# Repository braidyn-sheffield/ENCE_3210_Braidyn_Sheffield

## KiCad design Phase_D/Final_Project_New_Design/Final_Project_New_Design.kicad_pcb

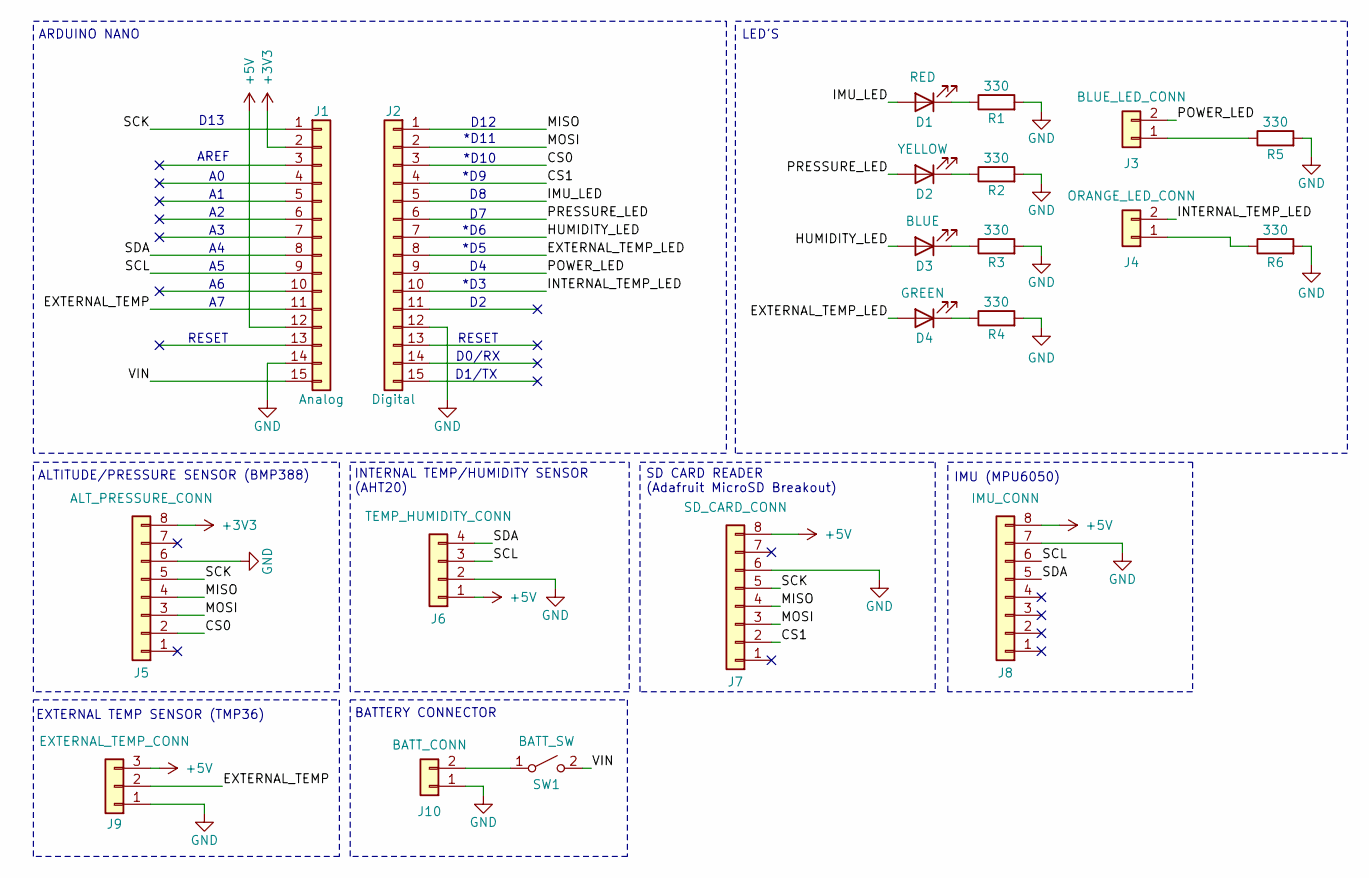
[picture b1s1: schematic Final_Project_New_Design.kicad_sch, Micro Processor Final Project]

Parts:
D1: RED; LED_D5.0mm
D2: YELLOW; LED_D5.0mm
D3: BLUE; LED_D5.0mm
D4: GREEN; LED_D5.0mm
J1: Analog; PinHeader_1x15_P2.54mm_Vertical
J2: Digital; PinHeader_1x15_P2.54mm_Vertical
J3: BLUE_LED_CONN; JST_PH_B2B-PH-K_1x02_P2.00mm_Vertical
J4: ORANGE_LED_CONN; JST_PH_B2B-PH-K_1x02_P2.00mm_Vertical
J5: ALT_PRESSURE_CONN; PinSocket_1x08_P2.54mm_Vertical
J6: TEMP_HUMIDITY_CONN; PinSocket_1x04_P2.54mm_Vertical
J7: SD_CARD_CONN; PinSocket_1x08_P2.54mm_Vertical
J8: IMU_CONN; PinSocket_1x08_P2.54mm_Vertical
J9: EXTERNAL_TEMP_CONN; JST_PH_B3B-PH-K_1x03_P2.00mm_Vertical
J10: BATT_CONN; Molex_KK-254_AE-6410-02A_1x02_P2.54mm_Vertical
R1, R2, R3, R4, R5, R6: 330; R_Axial_DIN0207_L6.3mm_D2.5mm_P7.62mm_Horizontal
SW1: BATT_SW; Toggle_SW

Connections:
+3V3: J1.2, J5.8
+5V: J1.12, J6.1, J7.8, J8.8, J9.3
/CS0: J2.3, J5.2
/CS1: J2.4, J7.2
/EXTERNAL_TEMP: J1.11, J9.2
/EXTERNAL_TEMP_LED: D4.2 (A), J2.8
/HUMIDITY_LED: D3.2 (A), J2.7
/IMU_LED: D1.2 (A), J2.5
/INTERNAL_TEMP_LED: J2.10, J4.2
/MISO: J2.1, J5.4, J7.4
/MOSI: J2.2, J5.3, J7.3
/POWER_LED: J2.9, J3.2
/PRESSURE_LED: D2.2 (A), J2.6
/SCK: J1.1, J5.5, J7.5
/SCL: J1.9, J6.3, J8.6
/SDA: J1.8, J6.4, J8.5
/VIN: J1.15, SW1.2 (B)
GND: J1.14, J2.12, J5.6, J6.2, J7.6, J8.7, J9.1, J10.1, R1.2, R2.2, R3.2, R4.2, R5.2, R6.2
unnamed: D1.1 (K), R1.1
unnamed: D2.1 (K), R2.1
unnamed: D3.1 (K), R3.1
unnamed: D4.1 (K), R4.1
unnamed: J3.1, R5.1
unnamed: J4.1, R6.1
unnamed: J10.2, SW1.1 (A)

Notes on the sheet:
D0/RX
D13
ALTITUDE/PRESSURE SENSOR (BMP388)
D1/TX
SD CARD READER (Adafruit MicroSD Breakout)
INTERNAL TEMP/HUMIDITY SENSOR (AHT20)
EXTERNAL TEMP SENSOR (TMP36)
*D9
RESET
*D10
IMU (MPU6050)
BATTERY CONNECTOR
D12
*D5
ARDUINO NANO
*D3
*D11
AREF
LED'S
*D6

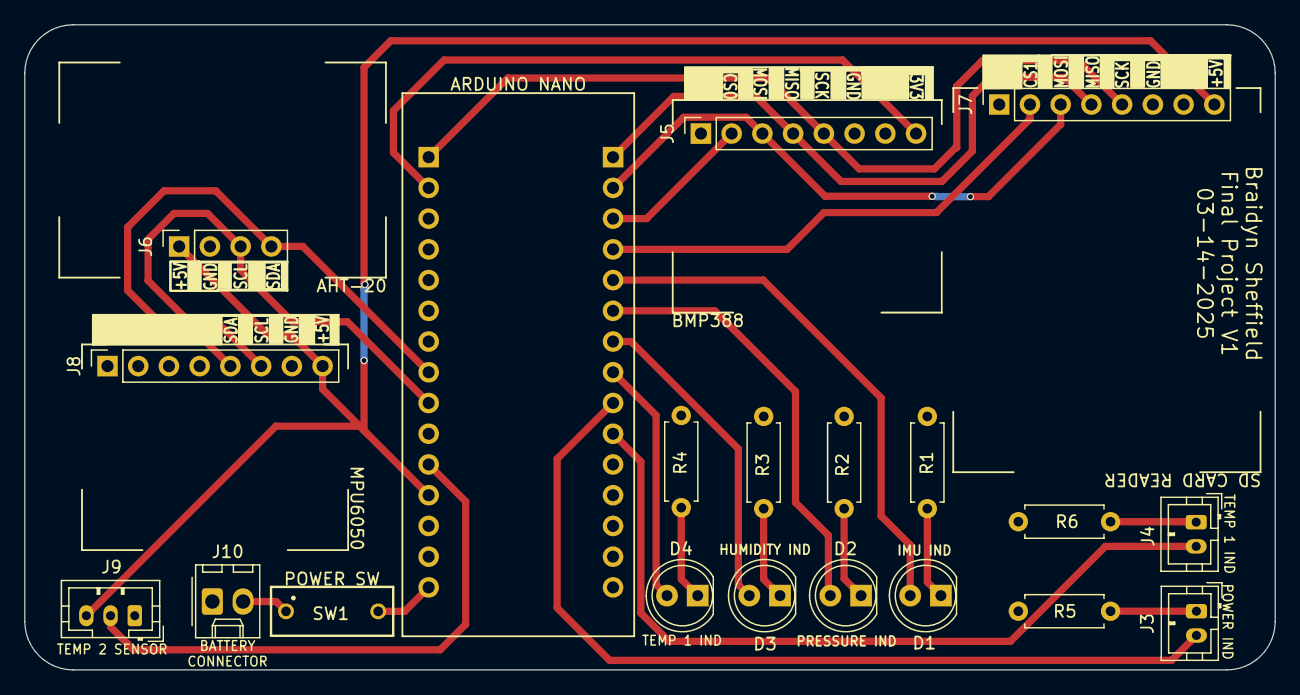
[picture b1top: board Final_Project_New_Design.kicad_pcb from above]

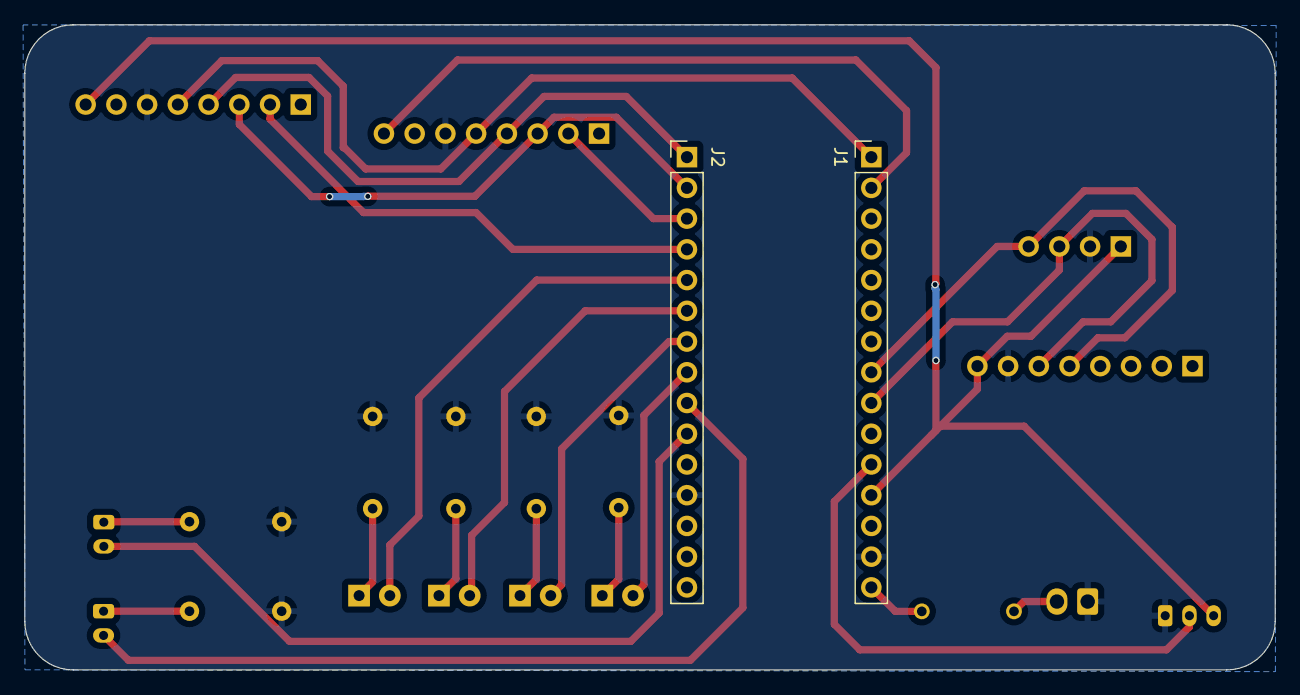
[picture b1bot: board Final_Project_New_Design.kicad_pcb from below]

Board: 2 copper layers, 103.4 x 53.3 mm, 21 parts (2 on the bottom side), 25 nets.

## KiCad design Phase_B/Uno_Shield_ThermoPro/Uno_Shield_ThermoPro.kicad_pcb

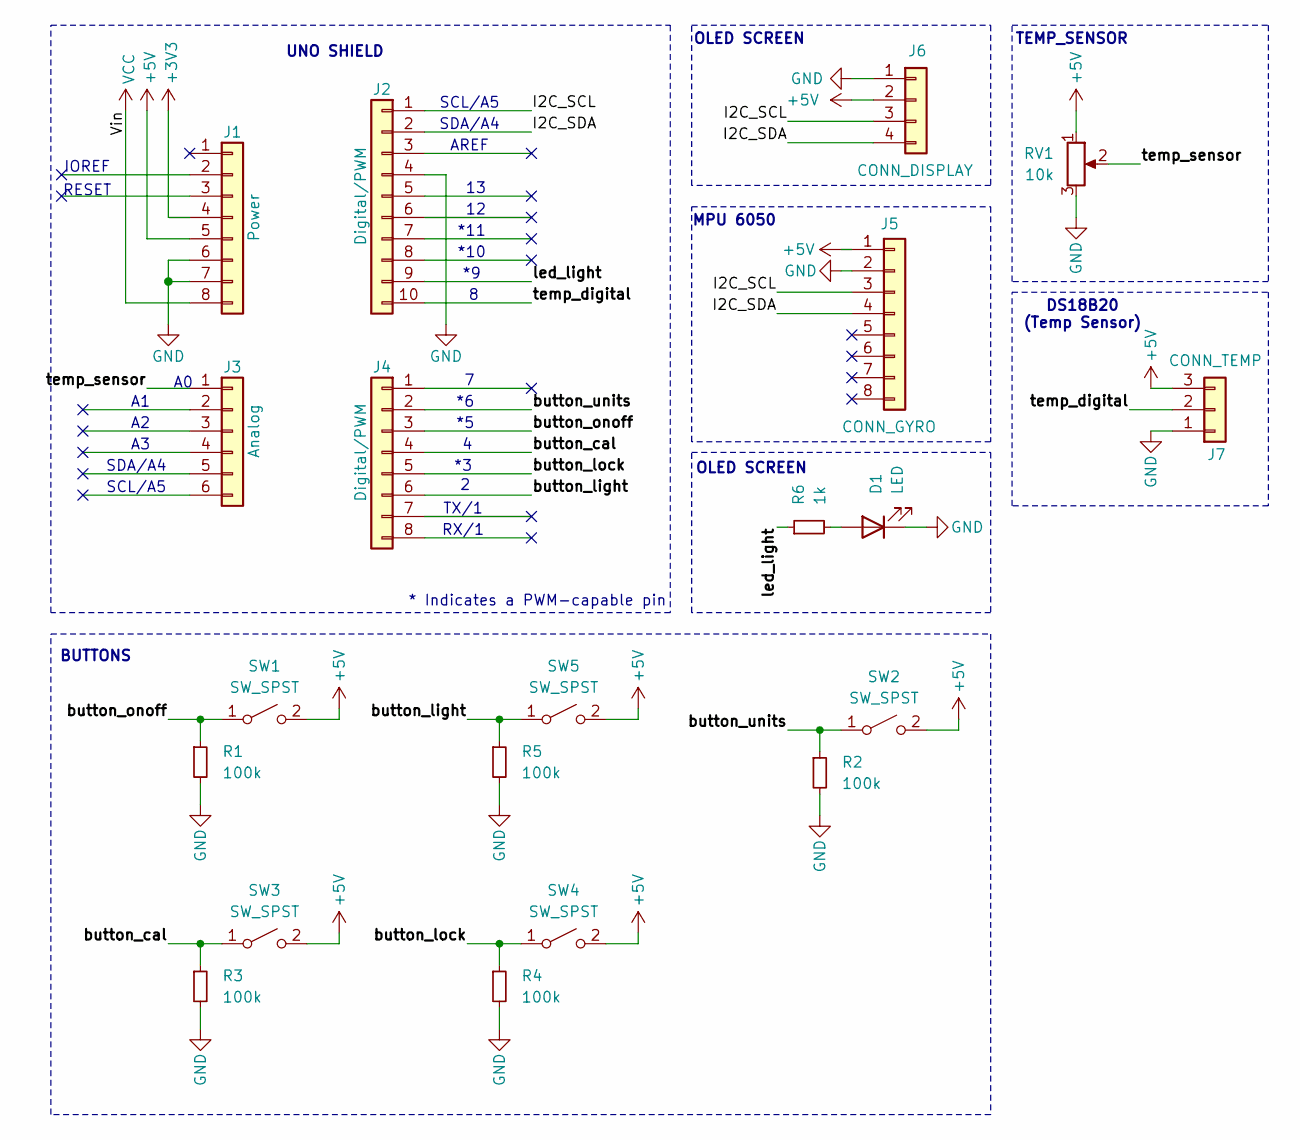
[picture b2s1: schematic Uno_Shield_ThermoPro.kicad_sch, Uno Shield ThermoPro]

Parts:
D1: LED; LED_D5.0mm
J1: Power; PinSocket_1x08_P2.54mm_Vertical
J2: Digital/PWM; PinSocket_1x10_P2.54mm_Vertical
J3: Analog; PinSocket_1x06_P2.54mm_Vertical
J4: Digital/PWM; PinSocket_1x08_P2.54mm_Vertical
J5: CONN_GYRO; PinSocket_1x08_P2.54mm_Vertical
J6: CONN_DISPLAY; PinSocket_1x04_P2.54mm_Vertical
J7: CONN_TEMP; JST_XH_B3B-XH-A_1x03_P2.50mm_Vertical
R1, R2, R3, R4, R5: 100k; R_Axial_DIN0207_L6.3mm_D2.5mm_P10.16mm_Horizontal
R6: 1k; R_Axial_DIN0207_L6.3mm_D2.5mm_P10.16mm_Horizontal
RV1: 10k; Potentiometer_Bourns_3386P_Vertical
SW1, SW2, SW3, SW4, SW5: SW_SPST; SW_PUSH_6mm

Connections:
+3V3: J1.4
+5V: J1.5, J5.1, J6.2, J7.3, RV1.1, SW1.2 (B), SW2.2 (B), SW3.2 (B), SW4.2 (B), SW5.2 (B)
/I2C_SCL: J2.1, J5.3, J6.3
/I2C_SDA: J2.2, J5.4, J6.4
/button_cal: J4.4, R3.1, SW3.1 (A)
/button_light: J4.6, R5.1, SW5.1 (A)
/button_lock: J4.5, R4.1, SW4.1 (A)
/button_onoff: J4.3, R1.1, SW1.1 (A)
/button_units: J4.2, R2.1, SW2.1 (A)
/led_light: J2.9, R6.1
/temp_digital: J2.10, J7.2
/temp_sensor: J3.1, RV1.2
GND: D1.1 (K), J1.6, J1.7, J2.4, J5.2, J6.1, J7.1, R1.2, R2.2, R3.2, R4.2, R5.2, RV1.3
unnamed: D1.2 (A), R6.2
VCC: J1.8

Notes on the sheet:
SDA/A4
MPU 6050
SCL/A5
DS18B20 (Temp Sensor)
*11
SDA/A4
TX/1
*10
SCL/A5
AREF
BUTTONS
UNO SHIELD
RESET
* Indicates a PWM-capable pin
RX/1
OLED SCREEN
IOREF
TEMP_SENSOR

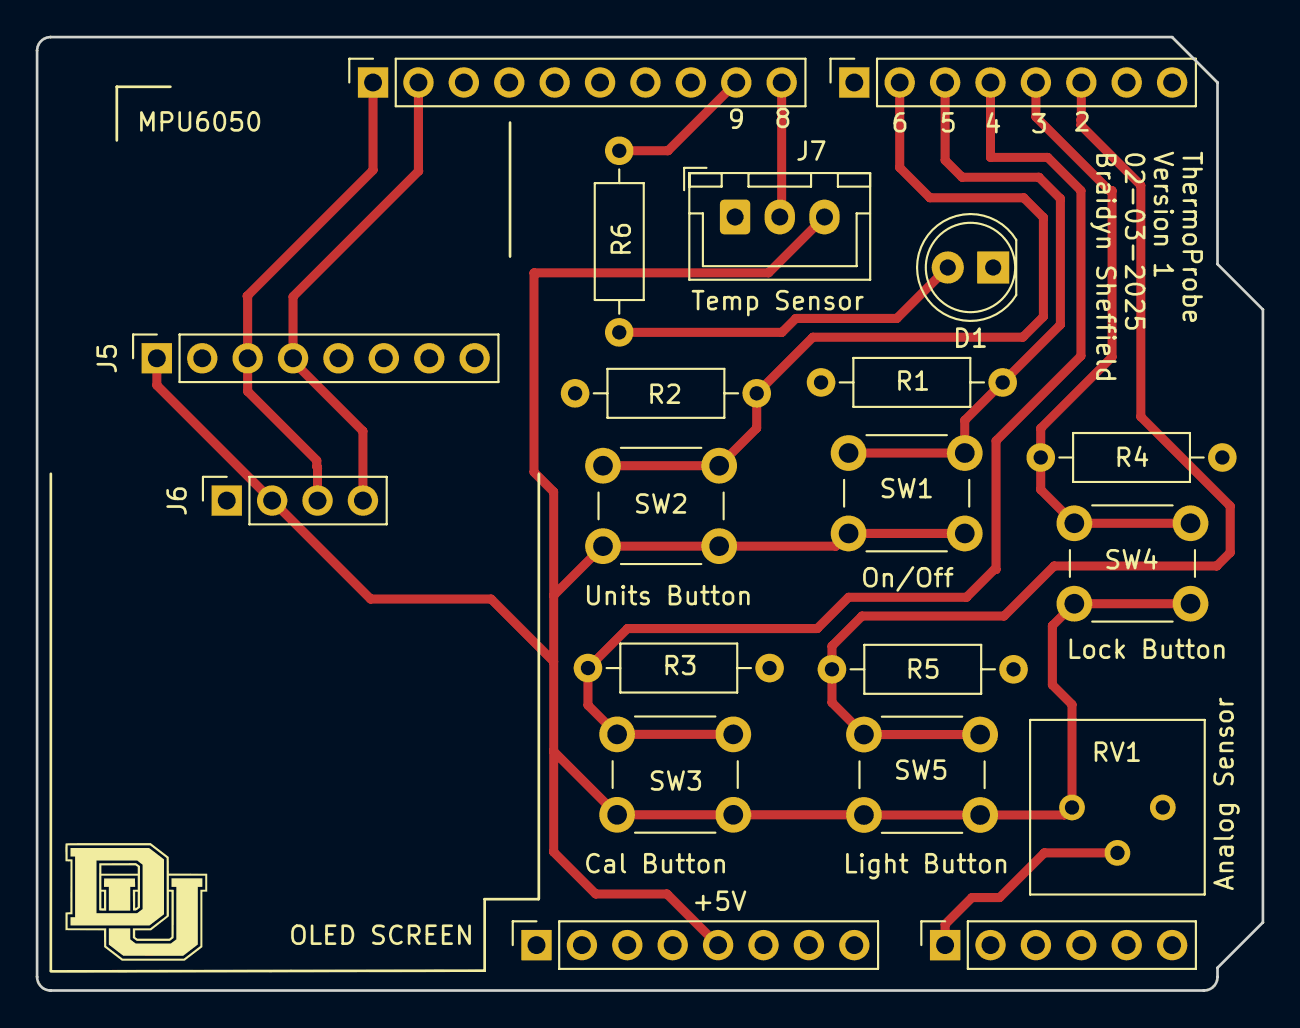
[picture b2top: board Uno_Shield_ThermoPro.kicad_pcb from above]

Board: 2 copper layers, 68.6 x 53.3 mm, 20 parts (0 on the bottom side), 13 nets.

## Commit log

2025-01-10 1/10 10:38 Adding Initial .ino files
2025-01-10 1-10 10:46 Adjusting folders under Lab 1
2025-01-12 1-11 20:26 Deleting random file
2025-01-15 1-14 21:42 Updated Part 2 and Part 3 of lab to match documentation requirements, as well as added Part 1 and Part 4 of Lab 1.
2025-01-16 1-15 20:37 Adding Part 5 to Lab 1.
2025-01-17 1-16 20:39 Adding Arduino code for Part 6.
2025-01-17 1-16 21:29 Adding Part 7 of the Lab.
2025-01-22 1-21 21:09 Adding all parts of the lab.
2025-01-31 1/30/2025 19:25 Adding code file and creating Lab 3 folder
2025-01-31 01/30/2025 19:45 Adding block diagram to Lab 3 folder
2025-01-31 0-31-2025 12:46 Adding Phase B files.
2025-02-03 02-02-2025 18:40 Updating Finalized Files
2025-02-03 02-03-2025 15:56 Updating Files
2025-02-04 02-03-2025 18:56 Updating files for Phase B.
2025-02-24 02-23-2025 23:47 Adding code for ThermoPro PCB Project
2025-02-26 02-25-2025 18:00 Adding Block Diagrams For Phase C
2025-02-27 02-27-2025 13:50 Adding Lab 4 Part 2 to Files
2025-02-28 02-27-2025 19:31 Adding part 3 of the lab to the files
2025-02-28 02-27-2025 23:05 Adding Files for Lab 4
2025-02-28 02-27-2025 23:09 Adding part 1 for lab 4
2025-03-14 03-13-2025 20:29 Adding files for Phase D
